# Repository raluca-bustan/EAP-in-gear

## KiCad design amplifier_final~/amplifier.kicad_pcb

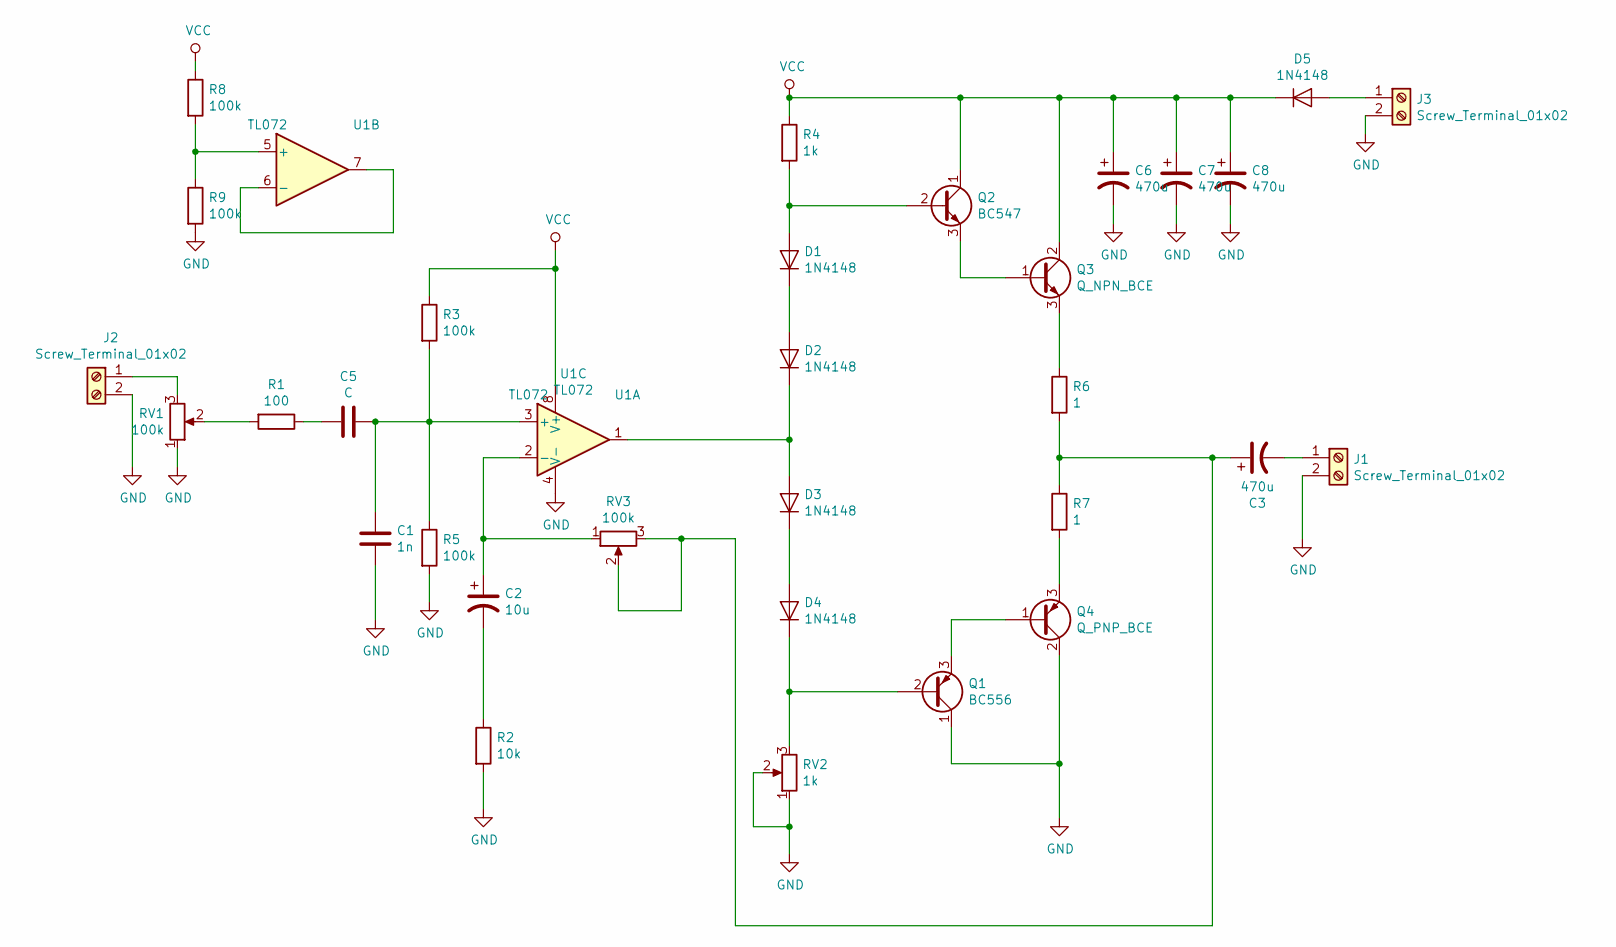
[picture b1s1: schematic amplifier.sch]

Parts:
C1: 1n; CP_Radial_D6.3mm_P2.50mm
C2: 10u; CP_Radial_D6.3mm_P2.50mm
C3, C6, C7, C8: 470u; CP_Radial_D8.0mm_P5.00mm
C5: C; CP_Radial_D8.0mm_P5.00mm
D1, D2, D3, D4, D5: 1N4148; D_DO-35_SOD27_P7.62mm_Horizontal
J1, J2, J3: Screw_Terminal_01x02; TerminalBlock_bornier-2_P5.08mm
Q1: BC556; TO-92_Inline
Q2: BC547; TO-92_Inline
Q3: Q_NPN_BCE; TO-220-3_Vertical
Q4: Q_PNP_BCE; TO-220-3_Vertical
R1: 100; R_Axial_DIN0204_L3.6mm_D1.6mm_P5.08mm_Horizontal
R2: 10k; R_Axial_DIN0204_L3.6mm_D1.6mm_P5.08mm_Horizontal
R3, R5, R8, R9: 100k; R_Axial_DIN0204_L3.6mm_D1.6mm_P5.08mm_Horizontal
R4: 1k; R_Axial_DIN0204_L3.6mm_D1.6mm_P5.08mm_Horizontal
R6, R7: 1; R_Axial_DIN0204_L3.6mm_D1.6mm_P5.08mm_Horizontal
RV1, RV3: 100k; Potentiometer_Bourns_3006P_Horizontal
RV2: 1k; Potentiometer_Bourns_3006P_Horizontal
U1: TL072; DIP-8_W7.62mm

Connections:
GND: C1.2, C6.2, C7.2, C8.2, J1.2, J2.2, J3.2, Q1.1 (C), Q4.2 (C), R2.2, R5.2, R9.2, RV1.1, RV2.1, RV2.2, U1.4 (V-)
unnamed: C1.1, C5.1, R3.2, R5.1, U1.3 (+)
unnamed: C2.1, RV3.1, U1.2 (-)
unnamed: C2.2, R2.1
unnamed: C3.1, R6.2, R7.1, RV3.2, RV3.3
unnamed: C3.2, J1.1
unnamed: C5.2, R1.1
unnamed: D1.1 (K), D2.2 (A)
unnamed: D1.2 (A), Q2.2 (B), R4.2
unnamed: D2.1 (K), D3.2 (A), U1.1
unnamed: D3.1 (K), D4.2 (A)
unnamed: D4.1 (K), Q1.2 (B), RV2.3
unnamed: D5.2 (A), J3.1
unnamed: J2.1, RV1.3
unnamed: Q1.3 (E), Q4.1 (B)
unnamed: Q2.3 (E), Q3.1 (B)
unnamed: Q3.3 (E), R6.1
unnamed: Q4.3 (E), R7.2
unnamed: R1.2, RV1.2
unnamed: R8.2, R9.1, U1.5 (+)
unnamed: U1.6 (-), U1.7
VCC: C6.1, C7.1, C8.1, D5.1 (K), Q2.1 (C), Q3.2 (C), R3.1, R4.1, R8.1, U1.8 (V+)

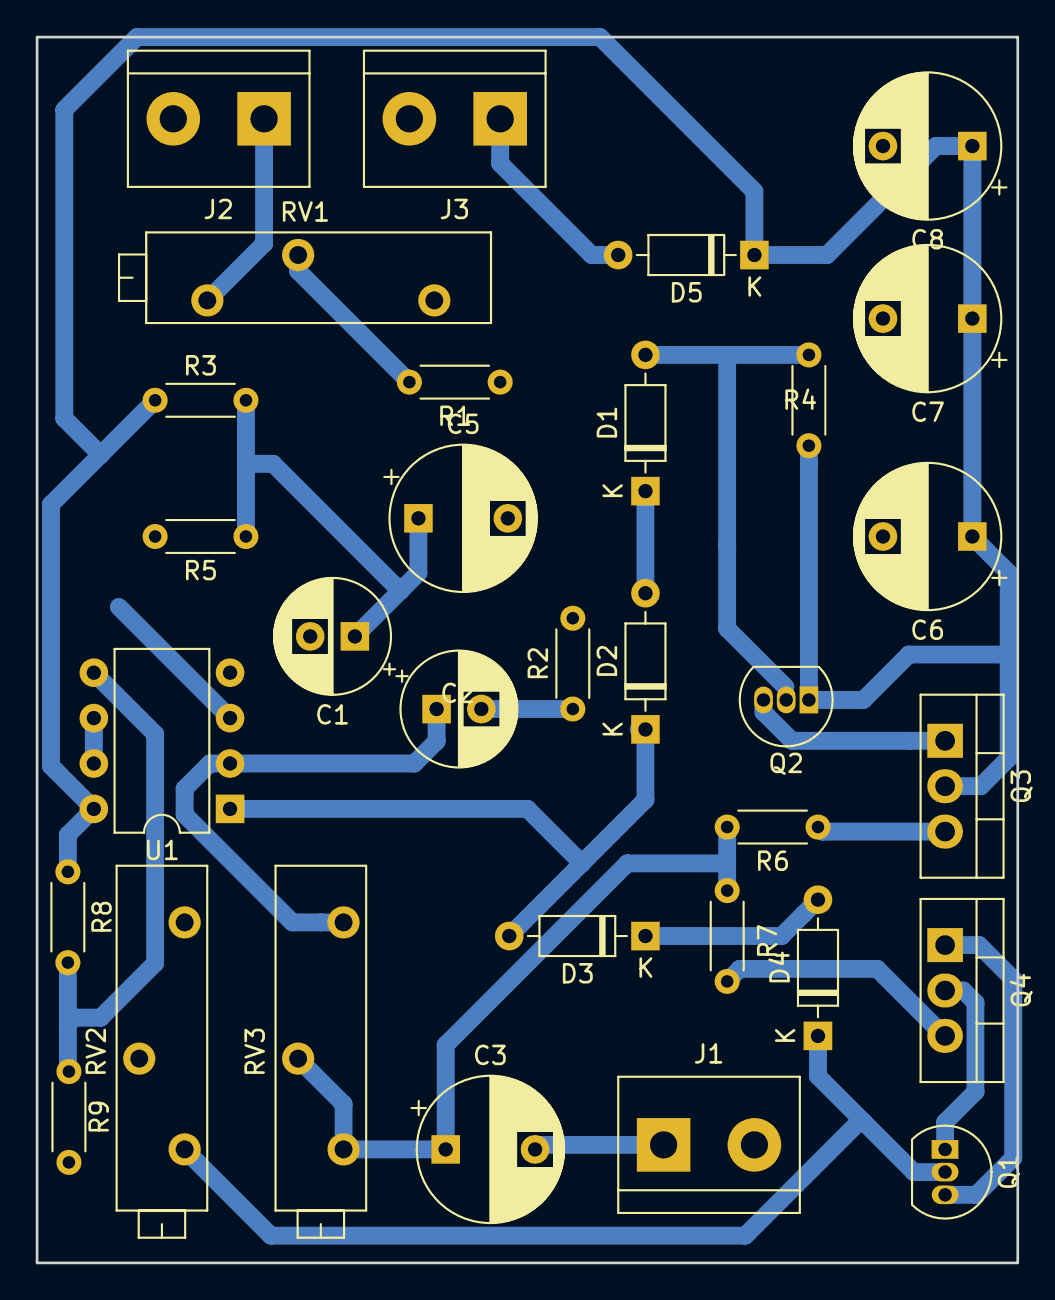
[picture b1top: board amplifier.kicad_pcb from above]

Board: 2 copper layers, 54.9 x 68.6 mm, 32 parts (0 on the bottom side), 22 nets.
